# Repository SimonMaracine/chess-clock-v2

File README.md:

# Chess Clock V2

Two years ago I made from scratch, together with a friend, a chess clock. We
used an Arduino Uno and some bought parts, like buttons, wires, an LCD screen
and other things like that, but everything else was made by us, including the
case and the internal wiring with a handmade PCB.

This time we would like to improve everything: the software, the case, the
wiring, the buttons and everything else.

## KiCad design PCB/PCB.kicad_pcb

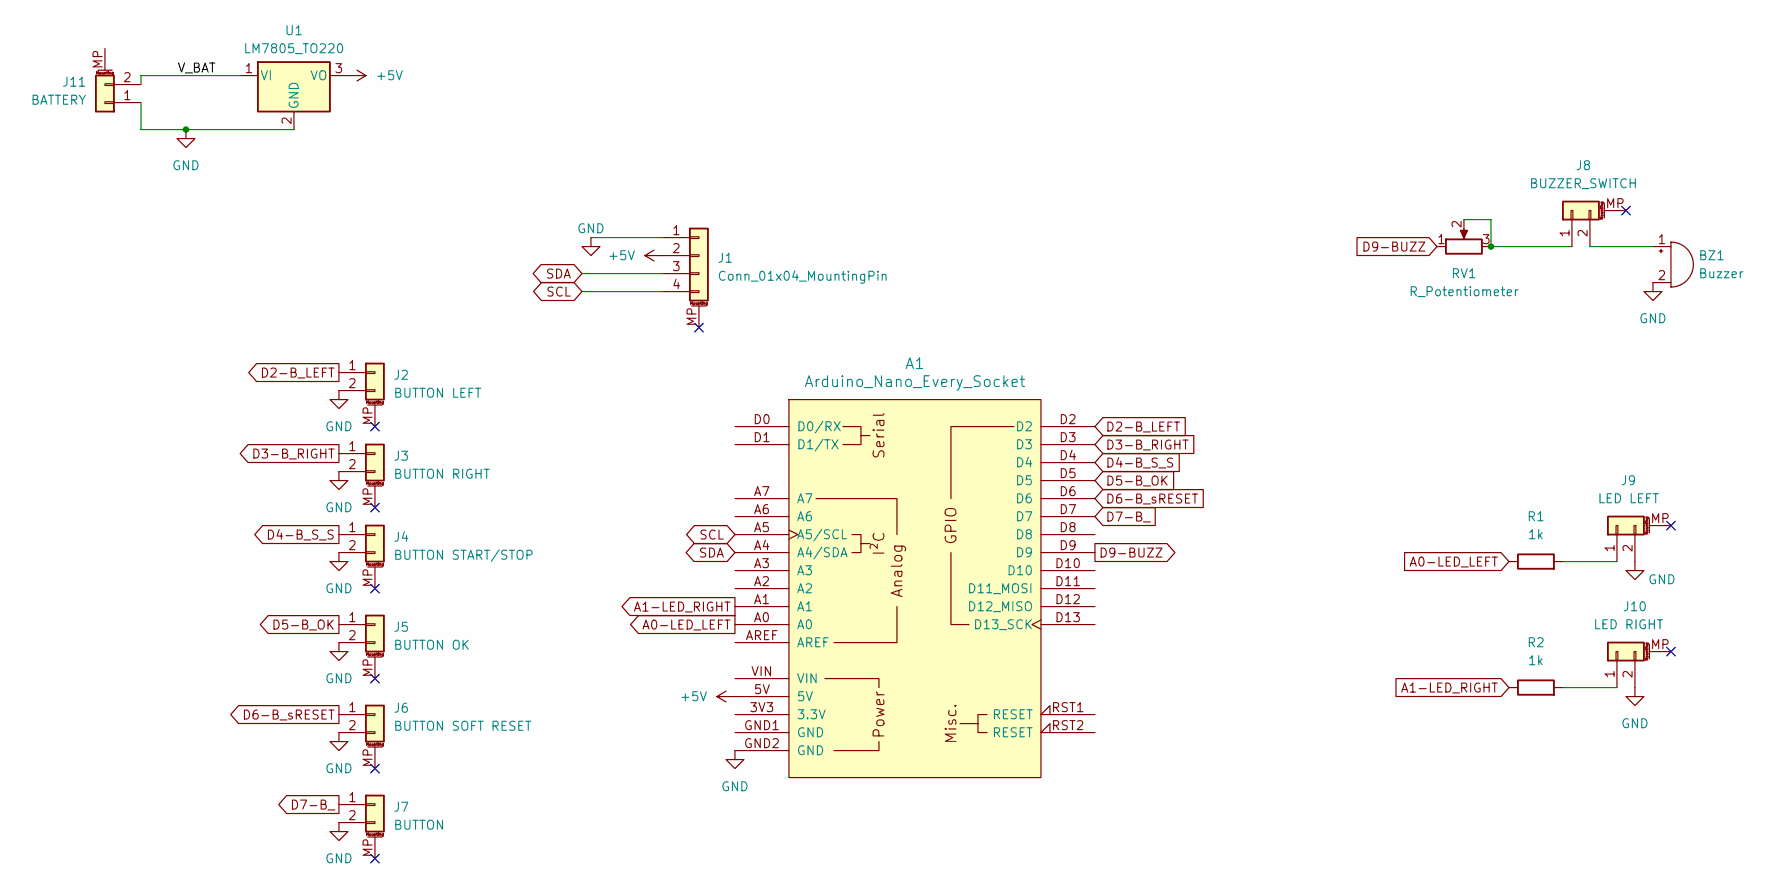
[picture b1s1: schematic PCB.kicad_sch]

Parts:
A1: Arduino_Nano_Every_Socket
BZ1: Buzzer; Buzzer_12x9.5RM7.6
J1: Conn_01x04_MountingPin; PinHeader_1x04_P2.54mm_Vertical
J2: BUTTON LEFT; PinHeader_1x02_P2.54mm_Vertical
J3: BUTTON RIGHT; PinHeader_1x02_P2.54mm_Vertical
J4: BUTTON START/STOP; PinHeader_1x02_P2.54mm_Vertical
J5: BUTTON OK; PinHeader_1x02_P2.54mm_Vertical
J6: BUTTON SOFT RESET; PinHeader_1x02_P2.54mm_Vertical
J7: BUTTON; PinHeader_1x02_P2.54mm_Vertical
J8: BUZZER_SWITCH; PinHeader_1x02_P2.54mm_Vertical
J9: LED LEFT; PinHeader_1x02_P2.54mm_Vertical
J10: LED RIGHT; PinHeader_1x02_P2.54mm_Vertical
J11: BATTERY; PinHeader_1x02_P2.54mm_Vertical
R1, R2: 1k; R_Axial_DIN0207_L6.3mm_D2.5mm_P10.16mm_Horizontal
RV1: R_Potentiometer; Potentiometer_ACP_CA9-V10_Vertical
U1: LM7805_TO220; TO-220-3_Vertical

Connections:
+5V: A1.5V, J1.2, U1.3 (VO)
/V_BAT: J11.2, U1.1 (VI)
A0-LED_LEFT: A1.A0, R1.1
A1-LED_RIGHT: A1.A1, R2.1
D2-B_LEFT: A1.D2, J2.1
D3-B_RIGHT: A1.D3, J3.1
D4-B_S_S: A1.D4, J4.1
D5-B_OK: A1.D5, J5.1
D6-B_sRESET: A1.D6, J6.1
D7-B_: A1.D7, J7.1
D9-BUZZ: A1.D9, RV1.1
GND: A1.GND1 (GND), A1.GND2 (GND), BZ1.2 (+), J1.1, J2.2, J3.2, J4.2, J5.2, J6.2, J7.2, J9.2, J10.2, J11.1, U1.2 (GND)
unnamed: BZ1.1 (-), J8.2
unnamed: J8.1, RV1.2, RV1.3
unnamed: J9.1, R1.2
unnamed: J10.1, R2.2
SCL: A1.A5 (A5/SCL), J1.4
SDA: A1.A4 (A4/SDA), J1.3

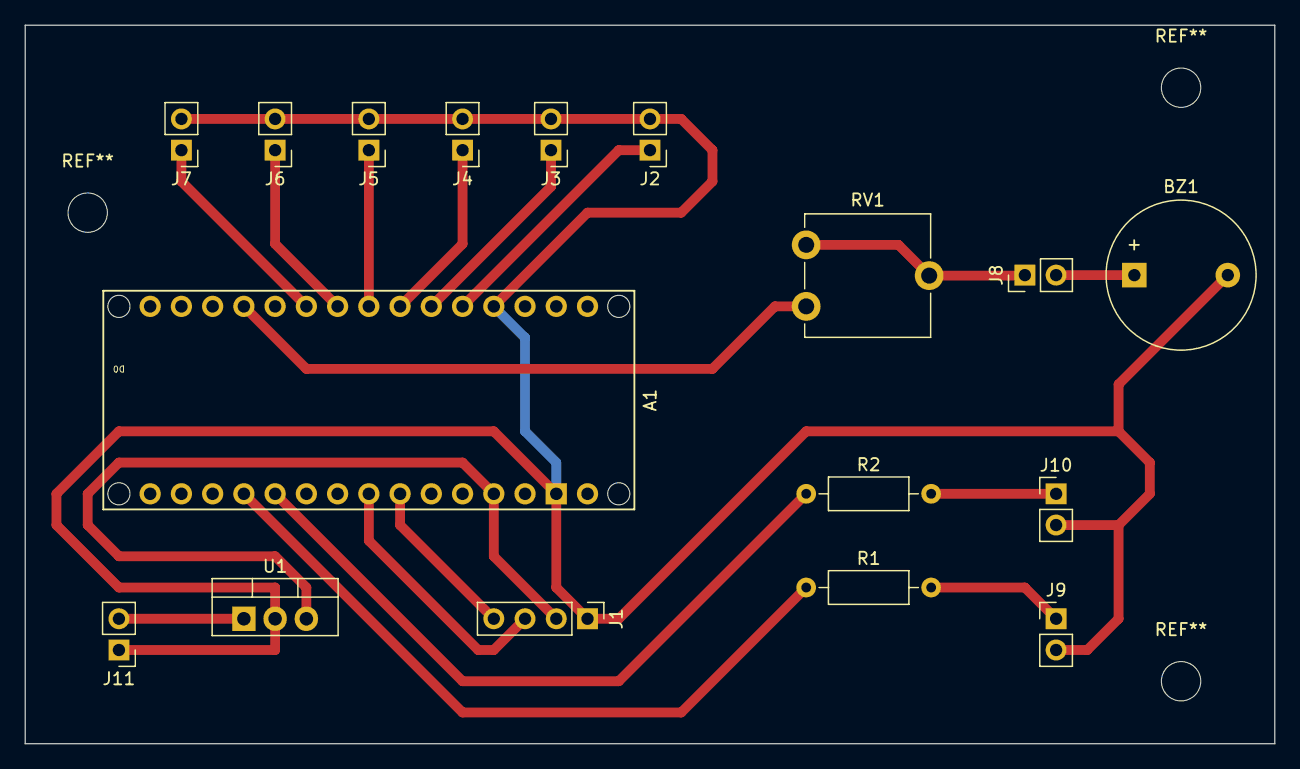
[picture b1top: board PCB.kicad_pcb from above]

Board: 4 copper layers, 101.6 x 58.4 mm, 17 parts (0 on the bottom side), 18 nets.

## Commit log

2023-09-11 Restructure the code; reimplement startup and menu states
2023-09-11 Make startup text random
2023-09-11 Create board schematic and footprint in kicad
2023-09-12 Rename source folder for consistency
2023-09-12 Work on the time setup and improve many things
2023-09-13 Reimplement two more states and improve many stuff
2023-09-14 Re-add stop method to states and fix a bug
2023-09-14 Implement three more modes
2023-09-14 Implement all modes
2023-09-14 Remove trailing whitespace
2023-09-15 Fix regression from rewriting everything
2023-09-15 Try to fix the buttons; not done
2023-09-16 Add something in README.md
2024-09-07 Clean up and improve the code
    It's still work in progress.
2024-09-07 Still work on refactoring
2024-09-09 Improve many things
2024-09-10 Fix some warnings
